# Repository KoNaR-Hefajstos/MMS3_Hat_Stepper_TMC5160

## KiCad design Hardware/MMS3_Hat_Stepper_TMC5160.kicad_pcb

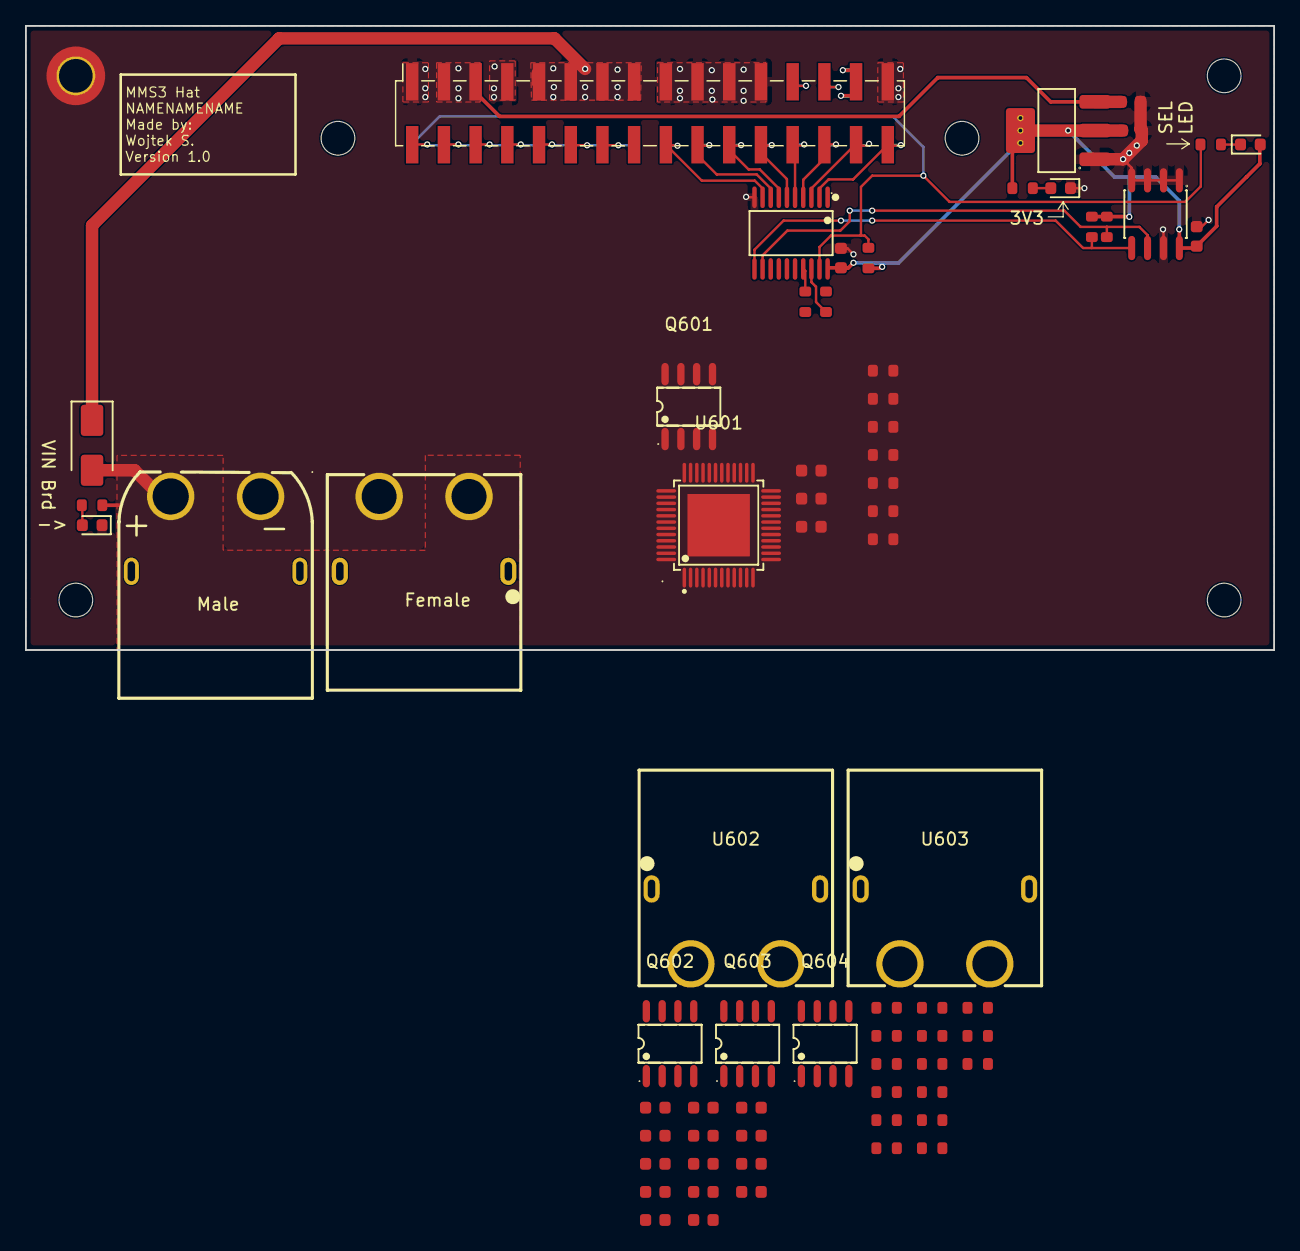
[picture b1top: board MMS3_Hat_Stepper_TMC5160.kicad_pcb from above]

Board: 2 copper layers, 100.0 x 50.0 mm, 75 parts (1 on the bottom side), 71 nets.

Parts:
C101, C102, C615, C616: 10uF; C_0603
C301, C501, C613, C614: 100nF; C_0603
C601: 2u2; C_0603
C602, C603: 22n; C_0603
C602#2, C603#2: 22nF; C_0603
C604: 2.2uF; C_0603
C605, C607, C612: 470nF; C_0603
C608, C609, C610, C611: 220nF; C_0603
CN401: XT60PW-M; C98732_CONN-TH_XT60PW-M
D101, D301, D402: Red; D_0603
D401: M7; D_SMA
H101: M2.5 Mount; MountingHole_2.7mm_M2.5_DIN965_Pad_TopOnly
H102, H103, H104, H105, H106: M2.5 mount; MountingHole_2.7mm_M2.5
J201: Chainbus in; PinHeader_2x16_P2.54mm_Vertical_SMD
J202: Chainbus Out; PinSocket_2x16_P2.54mm_Vertical_SMD
Q601, Q602, Q603, Q604: AO4882_C49020633; C49020633_SOIC-8_L4_9-W3_9-P1_27-LS6_0-BL
R101, R311: 1kΩ; R_0603
R301, R302, R303, R304, R305, R306, R307, R308, R309, R310: 10kΩ; R_0603
R312, R313: 0Ω; R_0603
R401: 27kΩ; R_0603
R601, R602, R610, R611: 47Ω; R_0603
R603, R612: 75mΩ; R_0603
R604, R605, R606, R607, R608, R609, R613, R614: 22Ω; R_0603
R615: 2.2Ω; R_0603
U101: AMS1117; SOT-223-3_L6.5-W3.4-P2.30-LS7.0-BR
U302: SN74CB3Q3245PWR; C470961_TSSOP-20_L6_5-W4_4-P0_65-LS6_4-BL
U401, U602, U603: XT60PW-F_C428722; C428722_TH_2P-XT60PW-F
U501: M24C64; SOIC-8_L5.0-W4.0-P1.27-LS6.0-BL
U601: TMC5160A-TA-T; C516354_TQFP-48_L7_0-W7_0-P0_50-LS9_0-BL-EP

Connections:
+3V3: C102.1, C301.1, C501.1, D301.2, R101.1, R301.1, R302.1, R304.1, R305.1, R306.1, R308.1, R310.1, U101.2 (VOUT), U101.4 (VOUT), U302.20 (VCC), U501.8 (VCC)
+5V: C101.1, C604.1, C605.1, J201.3, J201.5, J202.3, J202.5, R615.1, U101.3 (VIN), U601.21 (SD_MODE), U601.22 (SPI_MODE), U601.29 (VCC)
+12V stby: J201.29, J202.29
/Bus_switch/Chainbus.CS: R301.2, U302.13 (B6)
/Bus_switch/Chainbus.MISO: R307.1, U302.16 (B3)
/Bus_switch/Chainbus.MOSI: R309.1, U302.15 (B4)
/Bus_switch/Chainbus.RX: R306.2, R312.2
/Bus_switch/Chainbus.SCK: R302.2, R303.1, U302.14 (B5)
/Bus_switch/Chainbus.SCL: R304.2, U302.12 (B7), U501.6 (SCL)
/Bus_switch/Chainbus.SDA: R308.2, U302.11 (B8), U501.5 (SDA)
/Bus_switch/Chainbus.TX: R305.2, R313.2
/Bus_switch/Chainbus_In.CS: J201.22, J202.22, U302.7 (A6)
/Bus_switch/Chainbus_In.MISO: J201.28, J202.28, U302.4 (A3)
/Bus_switch/Chainbus_In.MOSI: J201.26, J202.26, U302.5 (A4)
/Bus_switch/Chainbus_In.RX: J201.32, J202.32, U302.2 (A1)
/Bus_switch/Chainbus_In.SCK: J201.24, J202.24, U302.6 (A5)
/Bus_switch/Chainbus_In.SCL: J201.20, J202.20, U302.8 (A7)
/Bus_switch/Chainbus_In.SDA: J201.18, J202.18, U302.9 (A8)
/Bus_switch/Chainbus_In.TX: J201.30, J202.30, U302.3 (A2)
/Bus_switch/Poka_Yoke_RX: R312.1, U302.18 (B1)
/Bus_switch/Poka_Yoke_TX: R313.1, U302.17 (B2)
/Bus_switch/SEL1: J201.2, R310.2, R311.1, U302.19 (OE#)
/Interboard_connector/Pin_25: J201.25, J202.25
/Interboard_connector/Pin_27: J201.27, J202.27
/Interboard_connector/SEL2: J201.4, J202.2
/Interboard_connector/SEL3: J201.6, J202.4
/Interboard_connector/SEL4: J201.8, J202.6
/Interboard_connector/SEL5: J201.10, J202.8
/Interboard_connector/SEL6: J201.12, J202.10
/Interboard_connector/SEL7: J201.14, J202.12
/Interboard_connector/SEL8: J201.16, J202.14
/Power Connector/VIN_BRD: C603.2, C603#2.2, C607.1, C612.1, C613.1, C614.1, C615.1, C616.1, CN401.2 (+), D401.2, Q601.5 (D), Q601.6 (D), Q601.7 (D), Q601.8 (D), Q603.5 (D), Q603.6 (D), Q603.7 (D), Q603.8 (D), R401.1, U401.3 (+), U601.4 (VSA), U601.33 (VS)
/User Area/Sterownik/BMA1: C608.2, Q601.3 (S), Q602.5 (D), Q602.6 (D), U601.40 (BMA1), U603.4 (-)
/User Area/Sterownik/BMA2: C609.2, Q601.1 (S), Q602.7 (D), Q602.8 (D), U601.37 (BMA2), U603.3 (+)
/User Area/Sterownik/BMB1: C610.2, Q603.3 (S), Q604.5 (D), Q604.6 (D), U601.48 (BMB1), U602.4 (-)
/User Area/Sterownik/BMB2: C611.2, Q603.1 (S), Q604.7 (D), Q604.8 (D), U601.45 (BMB2), U602.3 (+)
/User Area/Sterownik/CA1: C608.1, U601.42 (CA1)
/User Area/Sterownik/CA2: C609.1, U601.35 (CA2), U601.43 (CB2)
/User Area/Sterownik/CB1: C610.1, U601.2 (CB1)
/User Area/Sterownik/HA1: R604.1, U601.41 (HA1)
/User Area/Sterownik/HA2: R605.2, U601.36 (HA2)
/User Area/Sterownik/HB1: R608.1, U601.1 (HB1)
/User Area/Sterownik/HB2: R613.2, U601.44 (HB2)
/User Area/Sterownik/LA1: R607.1, U601.39 (LA1)
/User Area/Sterownik/LA2: R606.2, U601.38 (LA2)
/User Area/Sterownik/LB1: R609.1, U601.47 (LB1)
/User Area/Sterownik/LB2: R614.2, U601.46 (LB2)
/User Area/Sterownik/SRAH: R601.1, U601.8 (SRAH)
/User Area/Sterownik/SRAL: R602.1, U601.7 (SRAL)
/User Area/Sterownik/SRBH: R610.1, U601.9 (SRBH)
/User Area/Sterownik/SRBL: R611.1, U601.10 (SRBL)
GND: C101.2, C102.2, C301.2, C501.2, C601.1, C604.2, C605.2, C607.2, C612.2, C613.2, C614.2, C615.2, C616.2, CN401.1 (-), D101.1, D402.1, H101.1 (1_1), J201.1, J201.7, J201.17, J201.19, J201.21, J201.23, J201.31, J202.1, J202.7, J202.17, J202.19, J202.21, J202.23, J202.31, R303.2, R307.2, R309.2, R602.2, R603.2, R611.2, R612.2, U101.1 (GND), U302.10 (GND), U401.4 (-), U501.1 (A0), U501.2 (A1), U501.3 (A2), U501.4 (VSS), U501.7 (#WC), U601.6 (GNDA), U601.11 (TST_MODE), U601.12 (CLK), U601.19 (GNDD), U601.28 (DRV_ENN), U601.30 (GNDD), U601.49 (EP)
unnamed: D101.2, R101.2
unnamed: D301.1, R311.2
unnamed: D402.2, R401.2
unnamed: Q601.2 (G), R605.1
unnamed: Q601.4 (G), R604.2
unnamed: Q602.2 (G), R606.1
unnamed: Q602.1 (S), Q602.3 (S), R601.2, R603.1
unnamed: Q602.4 (G), R607.2
unnamed: Q603.2 (G), R613.1
unnamed: Q603.4 (G), R608.2
unnamed: Q604.2 (G), R614.1
unnamed: Q604.1 (S), Q604.3 (S), R610.2, R612.1
unnamed: Q604.4 (G), R609.2
unnamed: R615.2, U601.5 (5VOUT)
unnamed: C601.2, U601.3 (12VOUT)
unnamed: C602.1, C602#2.1, U601.32 (CPI)
unnamed: C602.2, C602#2.2, U601.31 (CPO)
unnamed: C603.1, C603#2.1, U601.34 (VCP)
VIN_CHAINBUS: D401.1, J201.9, J201.11, J201.13, J201.15, J202.9, J202.11, J202.13, J202.15
